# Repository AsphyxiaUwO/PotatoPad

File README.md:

# PotatoPad
by Austin Kim (@AsphyxiaUwO)
"The most of potato of potatopads"

This is a 4-key macropod with a 0.91-inch OLED display. It is also my submission for HackPad and the Highway to Undercity hackathon.
I have never worked with circuitry before, so this was a great first-time experience with KiCad. I am sure I learned a lot with this project.
I have used CAD software like Onshape previously, so I attempted to create a more complex case in compensation for the rather boring PCB design. I mount the screws through the bottom and place the heatset inserts on the top so that I do not let the screw stick out.

# Images
| Schematic | PCB | Case |
| -------- | ------- | ------- |
|  |  |  |

# Bill of Materials/Components
- 1x Custom 3d Printed Case
- 1x Custom PCB
- 1x 0.91" 128x32 OLED (SSD1306)
- 4x Cherry MX Switch
- 4x DSA Keycaps
- 1x Seeed XIAO RP2040
- 4x Heatset Inserts
- 4x M3x16mm screws

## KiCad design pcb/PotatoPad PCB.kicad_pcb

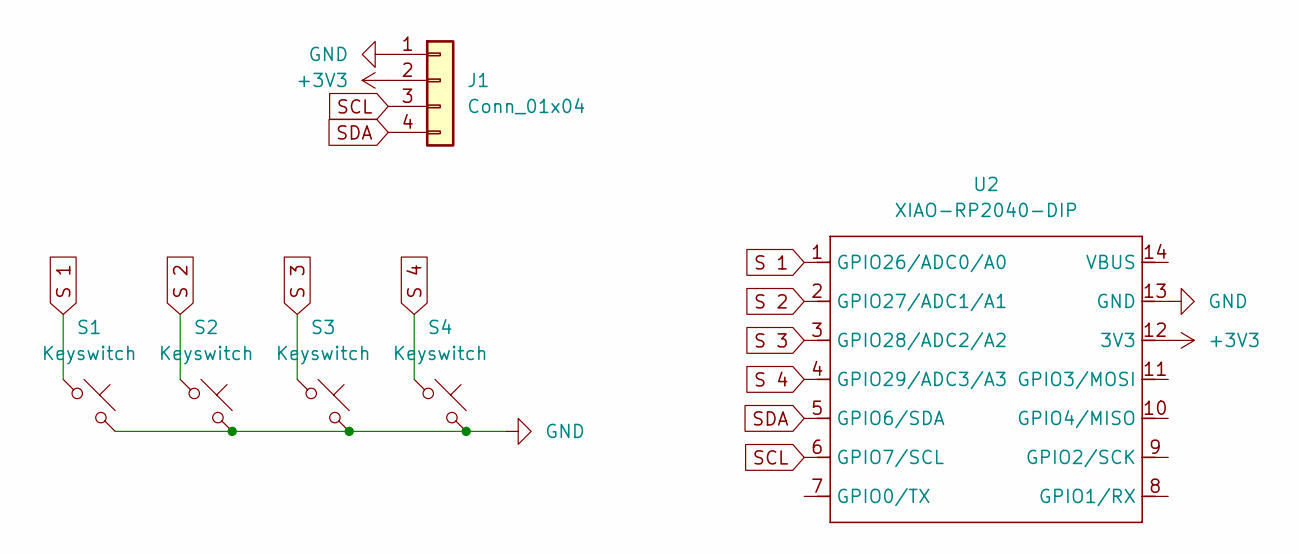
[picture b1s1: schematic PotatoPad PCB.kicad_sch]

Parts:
J1: Conn_01x04; SSD1306-0.91-OLED-4pin-128x32
S1, S2, S3, S4: Keyswitch; MX_PCB_1.00u
U2: XIAO-RP2040-DIP

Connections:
+3V3: J1.2, U2.12 (3V3)
GND: J1.1, S1.2, S2.2, S3.2, S4.2, U2.13 (GND)
S 1: S1.1, U2.1 (GPIO26/ADC0/A0)
S 2: S2.1, U2.2 (GPIO27/ADC1/A1)
S 3: S3.1, U2.3 (GPIO28/ADC2/A2)
S 4: S4.1, U2.4 (GPIO29/ADC3/A3)
SCL: J1.3, U2.6 (GPIO7/SCL)
SDA: J1.4, U2.5 (GPIO6/SDA)

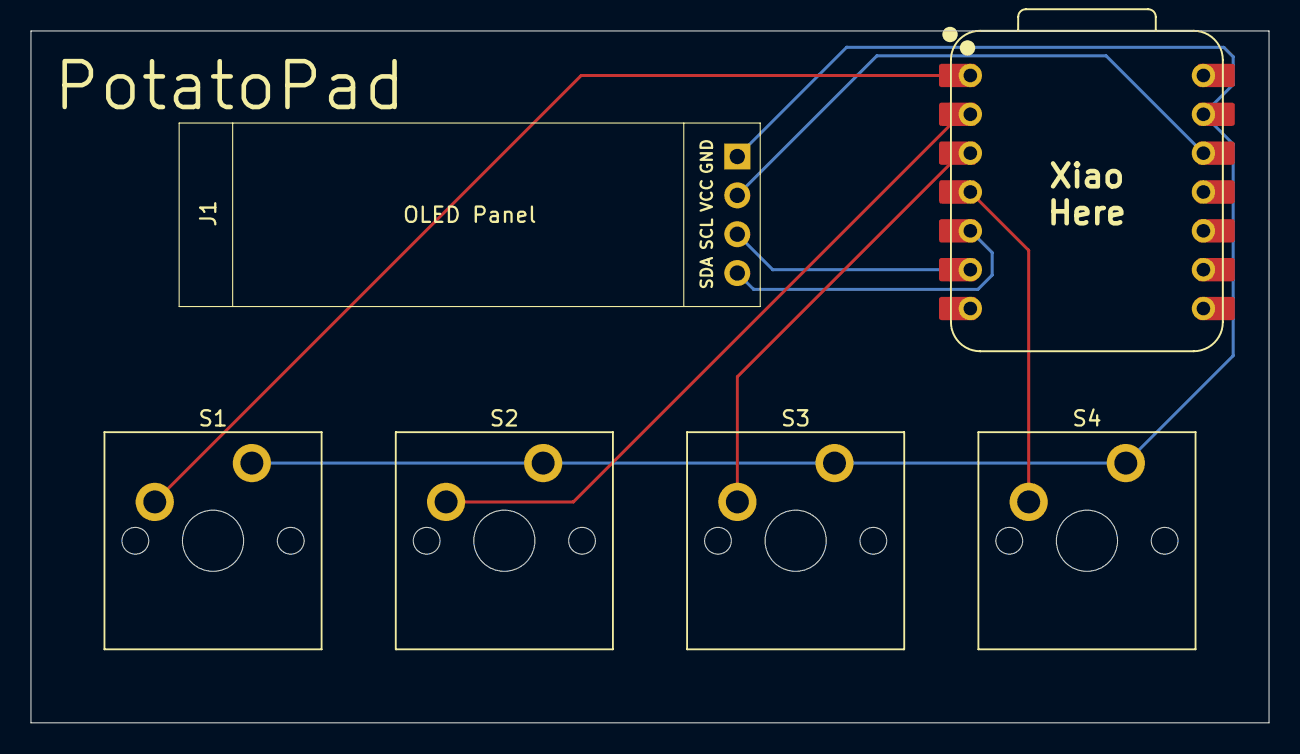
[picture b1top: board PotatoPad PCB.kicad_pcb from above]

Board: 2 copper layers, 81.0 x 45.2 mm, 6 parts (0 on the bottom side), 8 nets.
